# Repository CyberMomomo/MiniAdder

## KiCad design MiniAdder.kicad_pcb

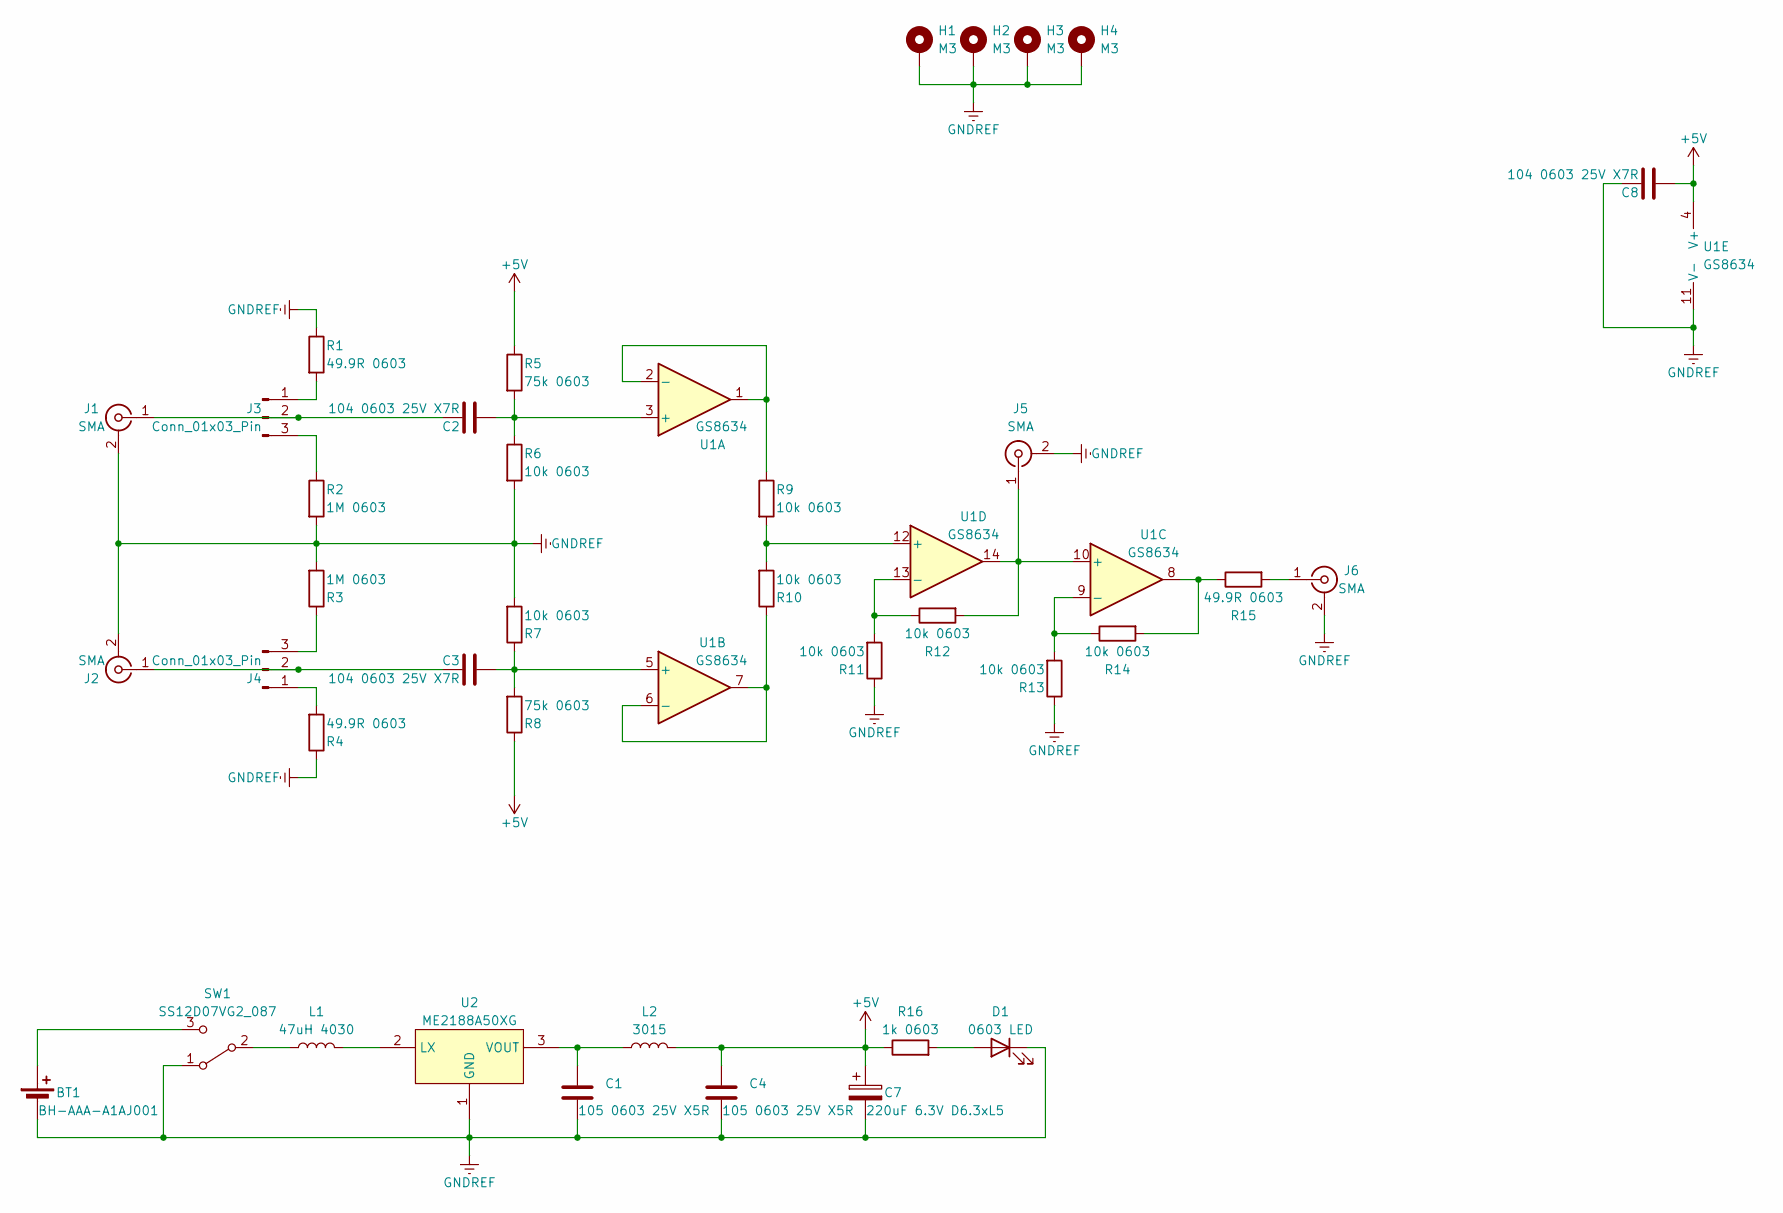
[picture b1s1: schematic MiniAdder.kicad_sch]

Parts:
BT1: BH-AAA-A1AJ001
C1, C4: 105 0603 25V X5R; C_0603_1608Metric
C2, C3, C8: 104 0603 25V X7R; C_0603_1608Metric
C7: 220uF 6.3V D6.3xL5; CP_Radial_D6.3mm_P2.50mm
D1: 0603 LED; LED_0603_1608Metric
H1, H2, H3, H4: M3; MountingHole_3.2mm_M3_Pad
J1, J2, J5, J6: SMA; SMA-KE_1.6mm
J3, J4: Conn_01x03_Pin; PinHeader_1x03_P2.54mm_Vertical
L1: 47uH 4030; L_Changjiang_FNR4030S
L2: 3015; L_Changjiang_FNR3015S
R1, R4, R15: 49.9R 0603; R_0603_1608Metric
R2, R3: 1M 0603; R_0603_1608Metric
R5, R8: 75k 0603; R_0603_1608Metric
R6, R7, R9, R10, R11, R12, R13, R14: 10k 0603; R_0603_1608Metric
R16: 1k 0603; R_0603_1608Metric
SW1: SS12D07VG2_087
U1: GS8634; SO-14_3.9x8.65mm_P1.27mm
U2: ME2188A50XG; SOT-23-3

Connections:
+5V: C4.1, C7.1, C8.2, L2.2, R5.1, R8.1, R16.1, U1.4 (V+)
GNDREF: BT1.2 (-), C1.2, C4.2, C7.2, C8.1, D1.1 (K), H1.1, H2.1, H3.1, H4.1, J1.2 (Ext), J2.2 (Ext), J5.2 (Ext), J6.2 (Ext), R1.1, R2.2, R3.2, R4.1, R6.2, R7.2, R11.1, R13.1, SW1.1 (A), U1.11 (V-), U2.1 (GND)
unnamed: BT1.1 (+), SW1.3 (C)
unnamed: D1.2 (A), R16.2
unnamed: C2.1, J1.1 (In), J3.2
unnamed: C3.1, J2.1 (In), J4.2
unnamed: J3.1, R1.2
unnamed: J3.3, R2.1
unnamed: J4.1, R4.2
unnamed: J4.3, R3.1
unnamed: J5.1 (In), R12.2, U1.10 (+), U1.14
unnamed: J6.1 (In), R15.2
unnamed: R14.2, R15.1, U1.8
unnamed: L1.1, SW1.2 (B)
unnamed: C2.2, R5.2, R6.1, U1.3 (+)
unnamed: R9.1, U1.1, U1.2 (-)
unnamed: C3.2, R7.1, R8.2, U1.5 (+)
unnamed: R10.1, U1.6 (-), U1.7
unnamed: R13.2, R14.1, U1.9 (-)
unnamed: R9.2, R10.2, U1.12 (+)
unnamed: R11.2, R12.1, U1.13 (-)
unnamed: L1.2, U2.2 (LX)
unnamed: C1.1, L2.1, U2.3 (VOUT)

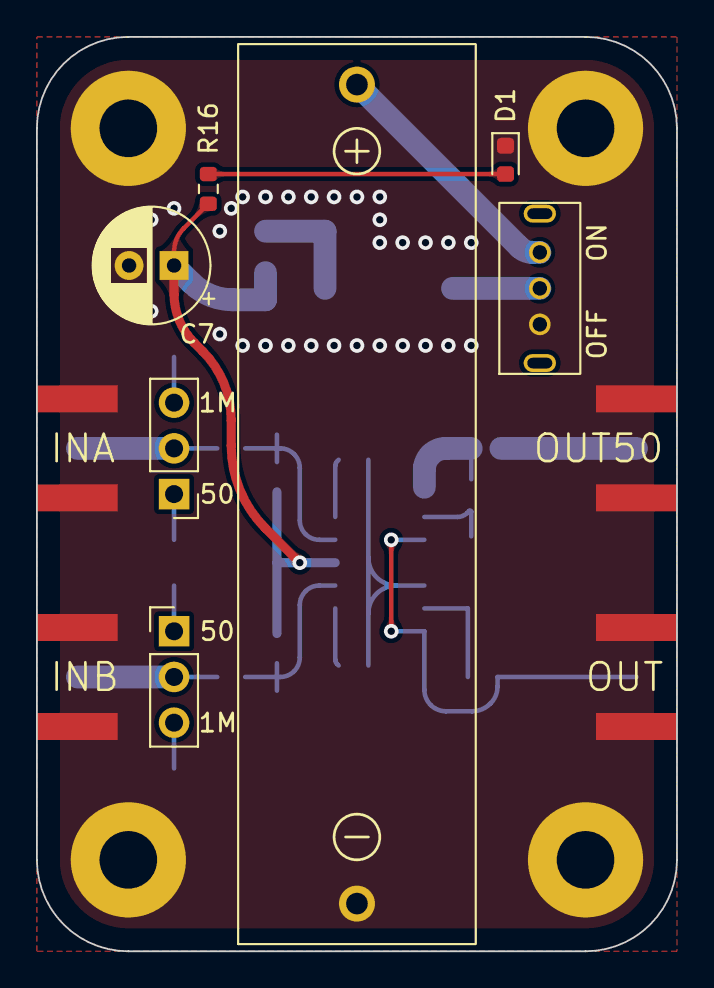
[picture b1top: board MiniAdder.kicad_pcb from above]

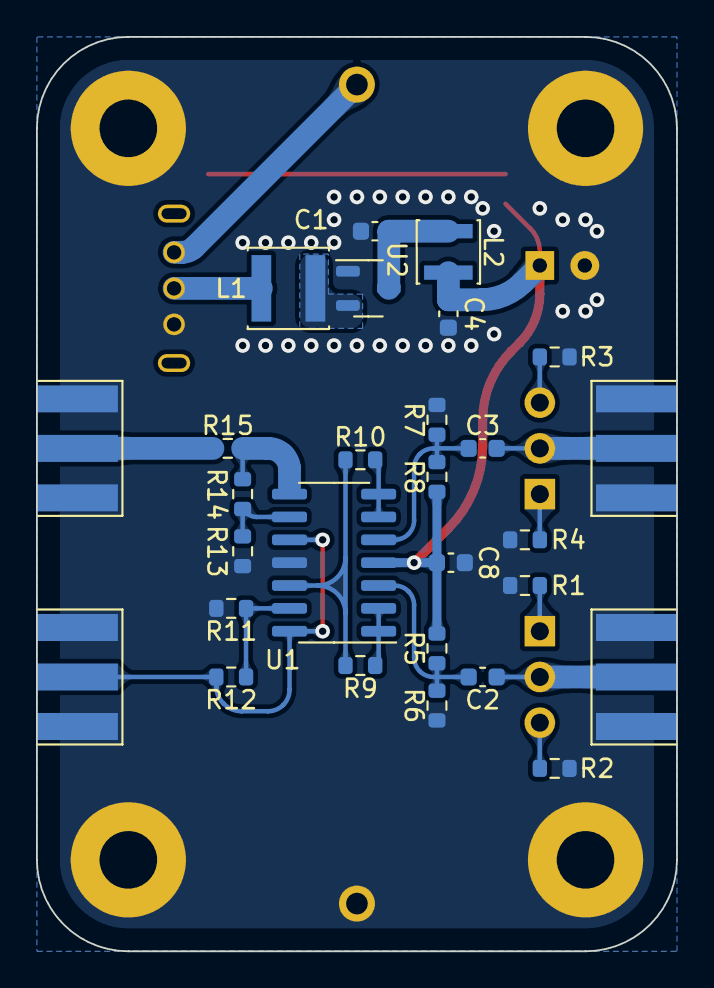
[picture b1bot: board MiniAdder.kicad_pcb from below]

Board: 2 copper layers, 35.6 x 50.8 mm, 39 parts (28 on the bottom side), 23 nets.

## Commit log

2024-02-27 Update Silkscreen
2024-02-27 Update version imformation
